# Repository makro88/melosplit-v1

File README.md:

# MeloSplit-v1

My first attempt at designing a custom keyboard, started as a challenge and as a potential new hobby.

Once I'm sure-ish this will actually work, I'm planning to build it as full wireless keyboard (thanks to [nice!nano](https://docs.nicekeyboards.com/#/nice!nano/))

Although it was supposed to be a simple ergo-split, it acquired a couple more functionalities along the way:
- wireless
- optional trrs
- hotswap MX switches
- RGB underglow
- RGB backlights
- rotary encoder
- reversible PCB

I lost count of how many times I've re-done the wiring in pcbnew, tried to keep it as tidy as possible!

### Kicad screenshots:

### Future plans:
- Make it work
- Cleaning up and adding some silks and text
- Case design

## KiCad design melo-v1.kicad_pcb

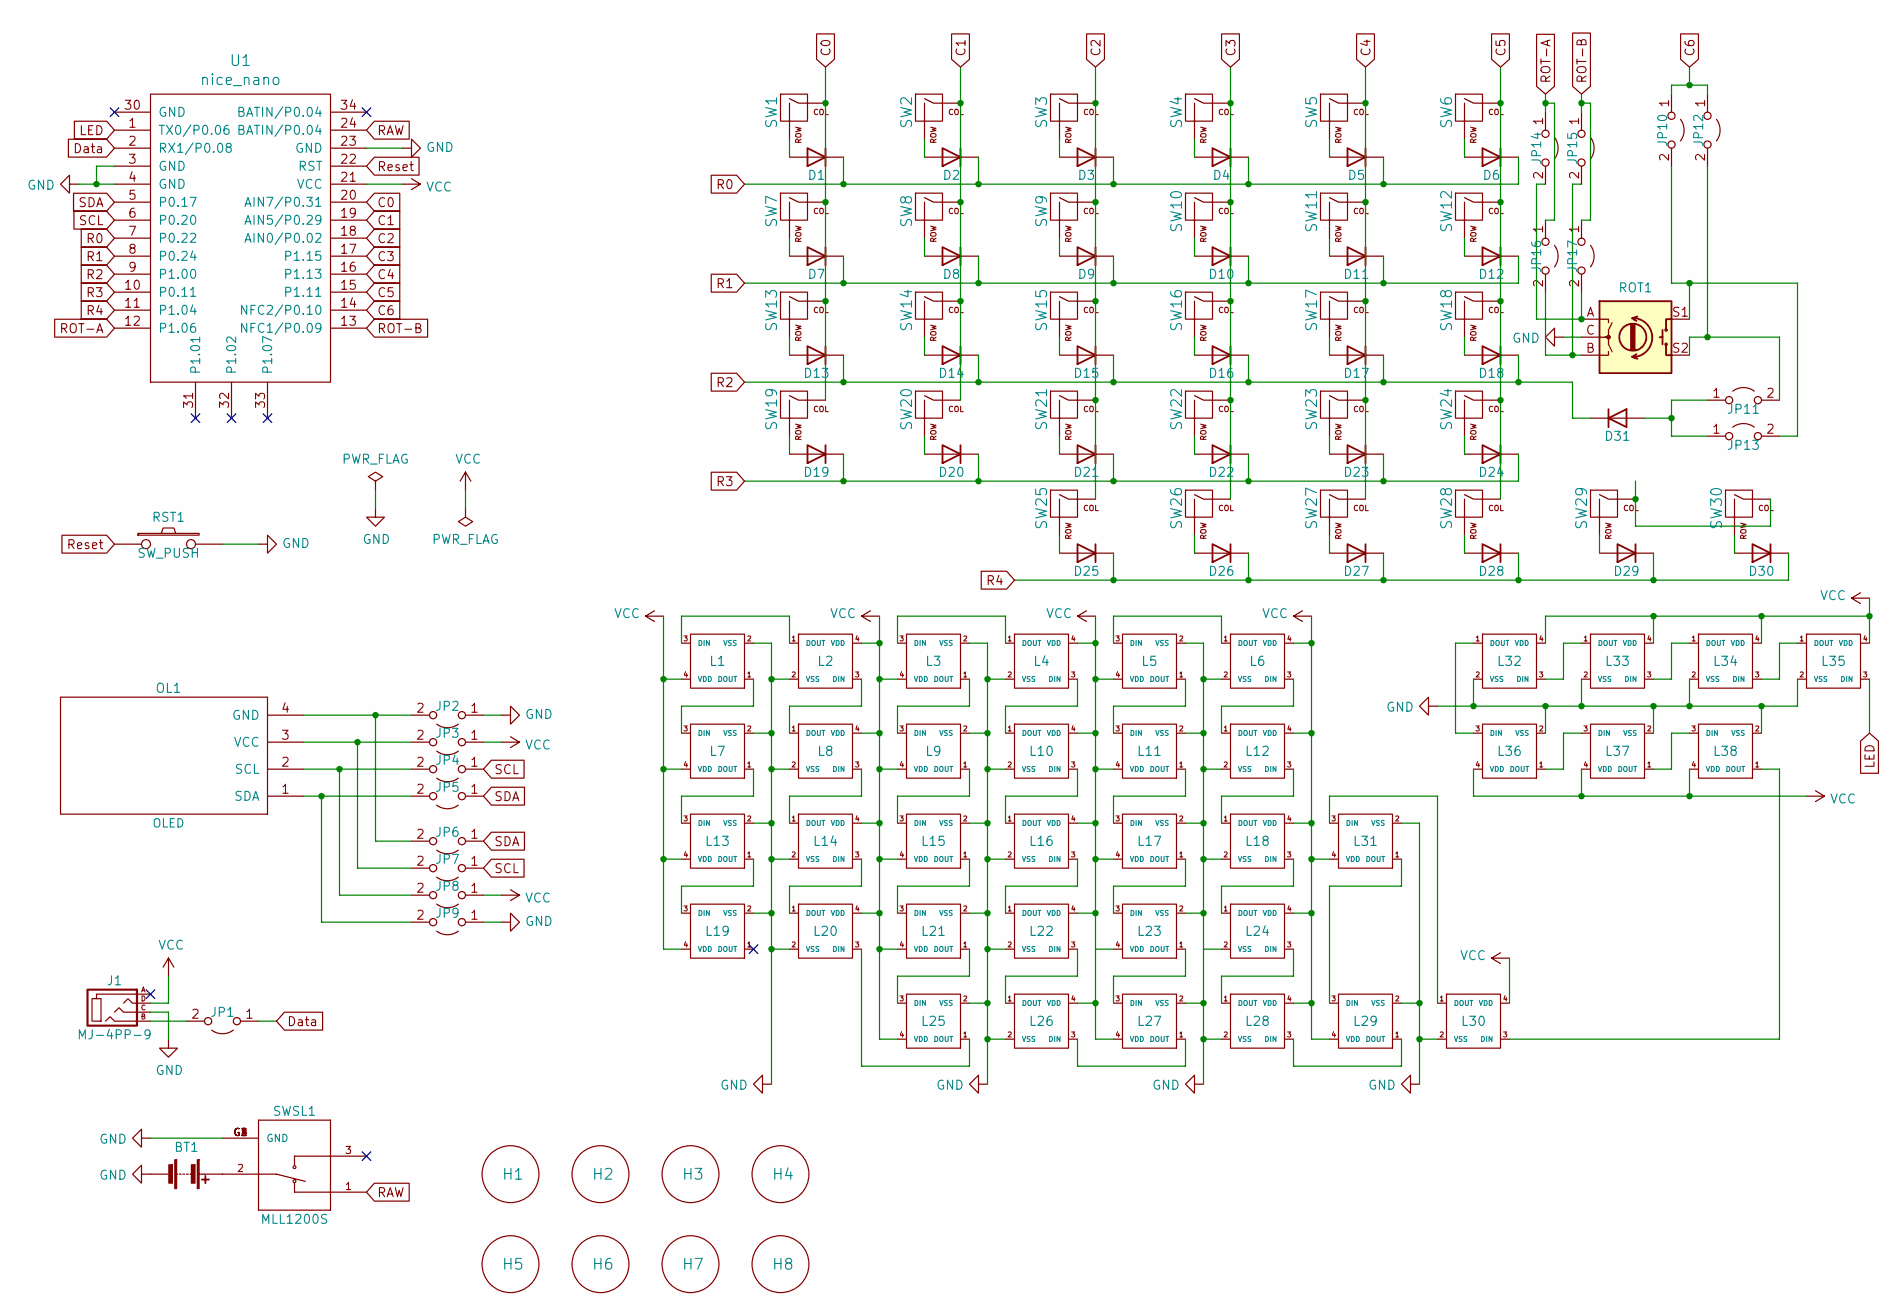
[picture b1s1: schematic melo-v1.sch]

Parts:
BT1: Battery; DF3A-3P-2DS_reversible
D1, D2, D3, D4, D5, D6, D7, D8, D9, D10, D11, D12, D13, D14, D15, D16, D17, D18, D19, D20, D21, D22, D23, D24, D25, D26, D27, D28, D29, D30, D31: D; D3_TH_SMD
H1, H2, H3, H4, H5, H6, H7, H8: Hole; HOLE
J1: MJ-4PP-9
JP1, JP2, JP3, JP4, JP5, JP6, JP7, JP8, JP9, JP10, JP11, JP12, JP13, JP14, JP15, JP16, JP17: Jumper_2_Open; Jumper
L1, L2, L3, L4, L5, L6, L7, L8, L9, L10, L11, L12, L13, L14, L15, L16, L17, L18, L19, L20, L21, L22, L23, L24, L25, L26, L27, L28, L29, L30, L31: SK6812MINI; YS-SK6812MINI-E_2sides
L32, L33, L34, L35, L36, L37, L38: SK6812MINI; SK6812MINI_underglow_rev
OL1: OLED
ROT1: Rotary_Encoder_Switch; RotaryEncoder_EC11
RST1: SW_PUSH; ResetSW
SW1, SW2, SW3, SW4, SW5, SW6, SW7, SW8, SW9, SW10, SW11, SW12, SW13, SW14, SW15, SW16, SW17, SW18, SW19, SW20, SW21, SW22, SW23, SW24, SW25, SW26, SW27, SW28, SW30: MX-NoLED; CherryMX_MidHeight_Hotswap
SW29: MX-NoLED; CherryMX_MidHeight_Hotswap_2U
SWSL1: MLL1200S; SW_MLL1200S
U1: nice_nano

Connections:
C0: SW1.1 (COL), SW7.1 (COL), SW13.1 (COL), SW19.1 (COL), U1.20 (AIN7/P0.31)
C1: SW2.1 (COL), SW8.1 (COL), SW14.1 (COL), SW20.1 (COL), U1.19 (AIN5/P0.29)
C2: SW3.1 (COL), SW9.1 (COL), SW15.1 (COL), SW21.1 (COL), SW25.1 (COL), U1.18 (AIN0/P0.02)
C3: SW4.1 (COL), SW10.1 (COL), SW16.1 (COL), SW22.1 (COL), SW26.1 (COL), U1.17 (P1.15)
C4: SW5.1 (COL), SW11.1 (COL), SW17.1 (COL), SW23.1 (COL), SW27.1 (COL), U1.16 (P1.13)
C5: SW6.1 (COL), SW12.1 (COL), SW18.1 (COL), SW24.1 (COL), SW28.1 (COL), U1.15 (P1.11)
C6: JP10.1 (A), JP12.1 (A), U1.14 (NFC2/P0.10)
Data: JP1.1 (A), U1.2 (RX1/P0.08)
LED: L35.3 (DIN), U1.1 (TX0/P0.06)
unnamed: BT1.1 (+), SWSL1.2
unnamed: D1.2 (A), SW1.2 (ROW)
unnamed: D2.2 (A), SW2.2 (ROW)
unnamed: D3.2 (A), SW3.2 (ROW)
unnamed: D4.2 (A), SW4.2 (ROW)
unnamed: D5.2 (A), SW5.2 (ROW)
unnamed: D6.2 (A), SW6.2 (ROW)
unnamed: D7.2 (A), SW7.2 (ROW)
unnamed: D8.2 (A), SW8.2 (ROW)
unnamed: D9.2 (A), SW9.2 (ROW)
unnamed: D10.2 (A), SW10.2 (ROW)
unnamed: D11.2 (A), SW11.2 (ROW)
unnamed: D12.2 (A), SW12.2 (ROW)
unnamed: D13.2 (A), SW13.2 (ROW)
unnamed: D14.2 (A), SW14.2 (ROW)
unnamed: D15.2 (A), SW15.2 (ROW)
unnamed: D16.2 (A), SW16.2 (ROW)
unnamed: D17.2 (A), SW17.2 (ROW)
unnamed: D18.2 (A), SW18.2 (ROW)
unnamed: D19.2 (A), SW19.2 (ROW)
unnamed: D20.2 (A), SW20.2 (ROW)
unnamed: D21.2 (A), SW21.2 (ROW)
unnamed: D22.2 (A), SW22.2 (ROW)
unnamed: D23.2 (A), SW23.2 (ROW)
unnamed: D24.2 (A), SW24.2 (ROW)
unnamed: D25.2 (A), SW25.2 (ROW)
unnamed: D26.2 (A), SW26.2 (ROW)
unnamed: D27.2 (A), SW27.2 (ROW)
unnamed: D28.2 (A), SW28.2 (ROW)
unnamed: D29.2 (A), SW29.2 (ROW)
unnamed: D30.2 (A), SW30.2 (ROW)
unnamed: D31.2 (A), JP11.1 (A), JP13.1 (A)
unnamed: J1.B, JP1.2 (B)
unnamed: JP2.2 (B), JP6.2 (B), OL1.4 (GND)
unnamed: JP3.2 (B), JP7.2 (B), OL1.3 (VCC)
unnamed: JP4.2 (B), JP8.2 (B), OL1.2 (SCL)
unnamed: JP5.2 (B), JP9.2 (B), OL1.1 (SDA)
unnamed: JP10.2 (B), JP13.2 (B), ROT1.S1
unnamed: JP11.2 (B), JP12.2 (B), ROT1.S2
unnamed: JP14.2 (B), JP17.2 (B), ROT1.A
unnamed: JP15.2 (B), JP16.2 (B), ROT1.B
unnamed: L1.1 (DOUT), L7.3 (DIN)
unnamed: L1.3 (DIN), L2.1 (DOUT)
unnamed: L2.3 (DIN), L8.1 (DOUT)
unnamed: L3.1 (DOUT), L9.3 (DIN)
unnamed: L3.3 (DIN), L4.1 (DOUT)
unnamed: L5.3 (DIN), L6.1 (DOUT)
unnamed: L4.3 (DIN), L10.1 (DOUT)
unnamed: L10.3 (DIN), L16.1 (DOUT)
unnamed: L11.1 (DOUT), L17.3 (DIN)
unnamed: L5.1 (DOUT), L11.3 (DIN)
unnamed: L6.3 (DIN), L12.1 (DOUT)
unnamed: L12.3 (DIN), L18.1 (DOUT)
unnamed: L13.1 (DOUT), L19.3 (DIN)
unnamed: L7.1 (DOUT), L13.3 (DIN)
unnamed: L8.3 (DIN), L14.1 (DOUT)
unnamed: L14.3 (DIN), L20.1 (DOUT)
unnamed: L15.1 (DOUT), L21.3 (DIN)
unnamed: L9.1 (DOUT), L15.3 (DIN)
unnamed: L16.3 (DIN), L22.1 (DOUT)
unnamed: L17.1 (DOUT), L23.3 (DIN)
unnamed: L18.3 (DIN), L24.1 (DOUT)
unnamed: L20.3 (DIN), L25.1 (DOUT)
unnamed: L21.1 (DOUT), L25.3 (DIN)
unnamed: L22.3 (DIN), L26.1 (DOUT)
unnamed: L23.1 (DOUT), L27.3 (DIN)
unnamed: L24.3 (DIN), L28.1 (DOUT)
unnamed: L26.3 (DIN), L27.1 (DOUT)
unnamed: L28.3 (DIN), L29.1 (DOUT)
unnamed: L29.3 (DIN), L31.1 (DOUT)
unnamed: L30.1 (DOUT), L31.3 (DIN)
unnamed: L30.3 (DIN), L38.1 (DOUT)
unnamed: L32.1 (DOUT), L36.3 (DIN)
unnamed: L32.3 (DIN), L33.1 (DOUT)
unnamed: L33.3 (DIN), L34.1 (DOUT)
unnamed: L34.3 (DIN), L35.1 (DOUT)
unnamed: L36.1 (DOUT), L37.3 (DIN)
unnamed: L37.1 (DOUT), L38.3 (DIN)
unnamed: SW29.1 (COL), SW30.1 (COL)
R0: D1.1 (K), D2.1 (K), D3.1 (K), D4.1 (K), D5.1 (K), D6.1 (K), U1.7 (P0.22)
R1: D7.1 (K), D8.1 (K), D9.1 (K), D10.1 (K), D11.1 (K), D12.1 (K), U1.8 (P0.24)
R2: D13.1 (K), D14.1 (K), D15.1 (K), D16.1 (K), D17.1 (K), D18.1 (K), D31.1 (K), U1.9 (P1.00)
R3: D19.1 (K), D20.1 (K), D21.1 (K), D22.1 (K), D23.1 (K), D24.1 (K), U1.10 (P0.11)
R4: D25.1 (K), D26.1 (K), D27.1 (K), D28.1 (K), D29.1 (K), D30.1 (K), U1.11 (P1.04)
RAW: SWSL1.1, U1.24 (BATIN/P0.04)
ROT-A: JP14.1 (A), JP16.1 (A), U1.12 (P1.06)
ROT-B: JP15.1 (A), JP17.1 (A), U1.13 (NFC1/P0.09)
Reset: RST1.1, U1.22 (RST)
SCL: JP4.1 (A), JP7.1 (A), U1.6 (P0.20)
SDA: JP5.1 (A), JP6.1 (A), U1.5 (P0.17)

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
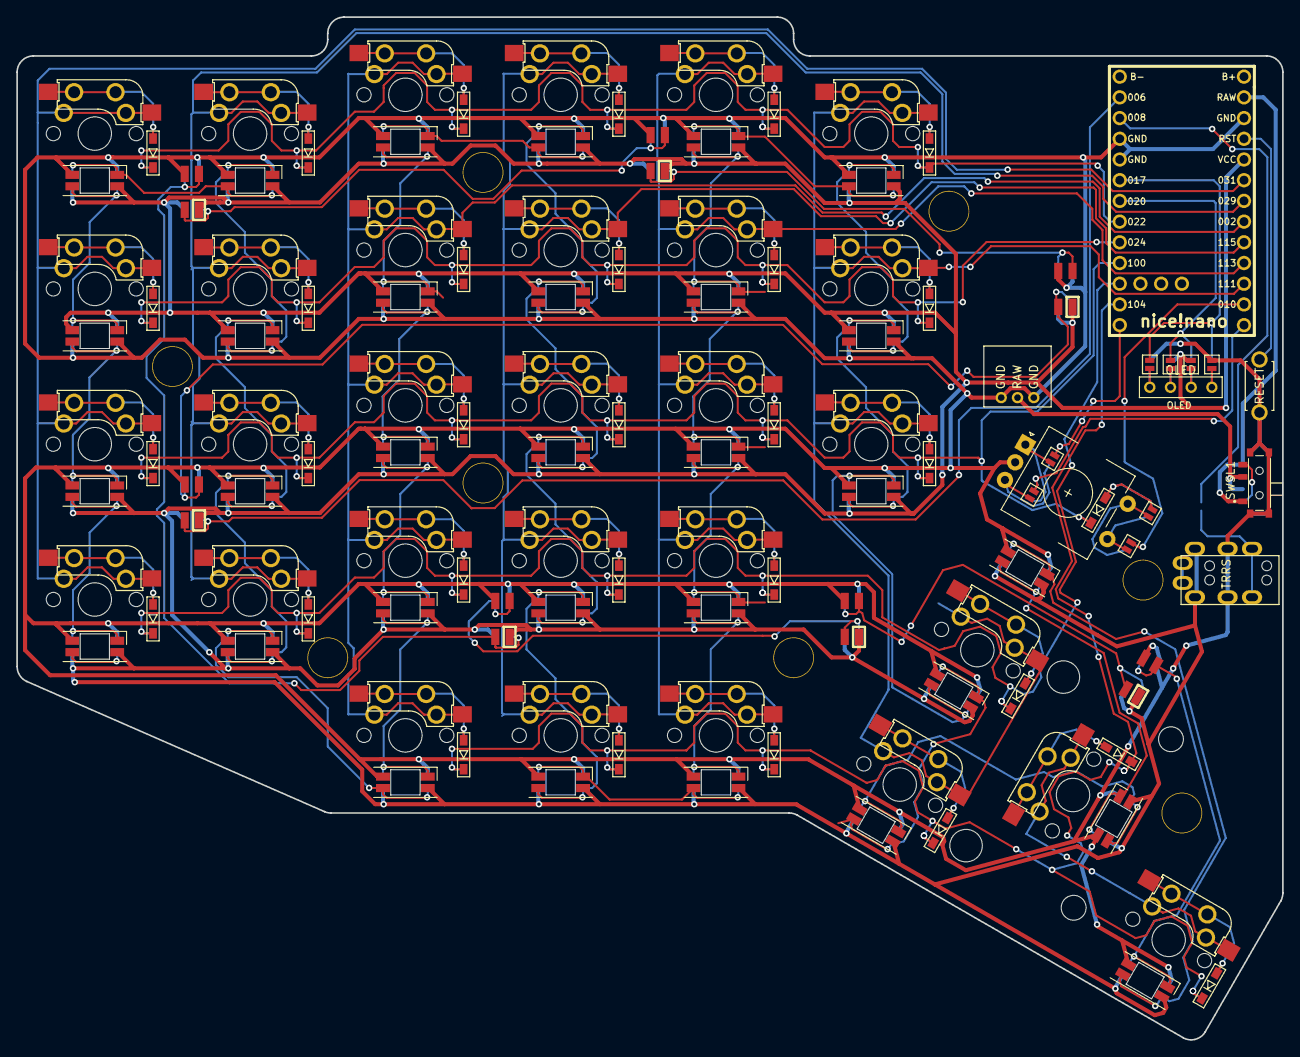
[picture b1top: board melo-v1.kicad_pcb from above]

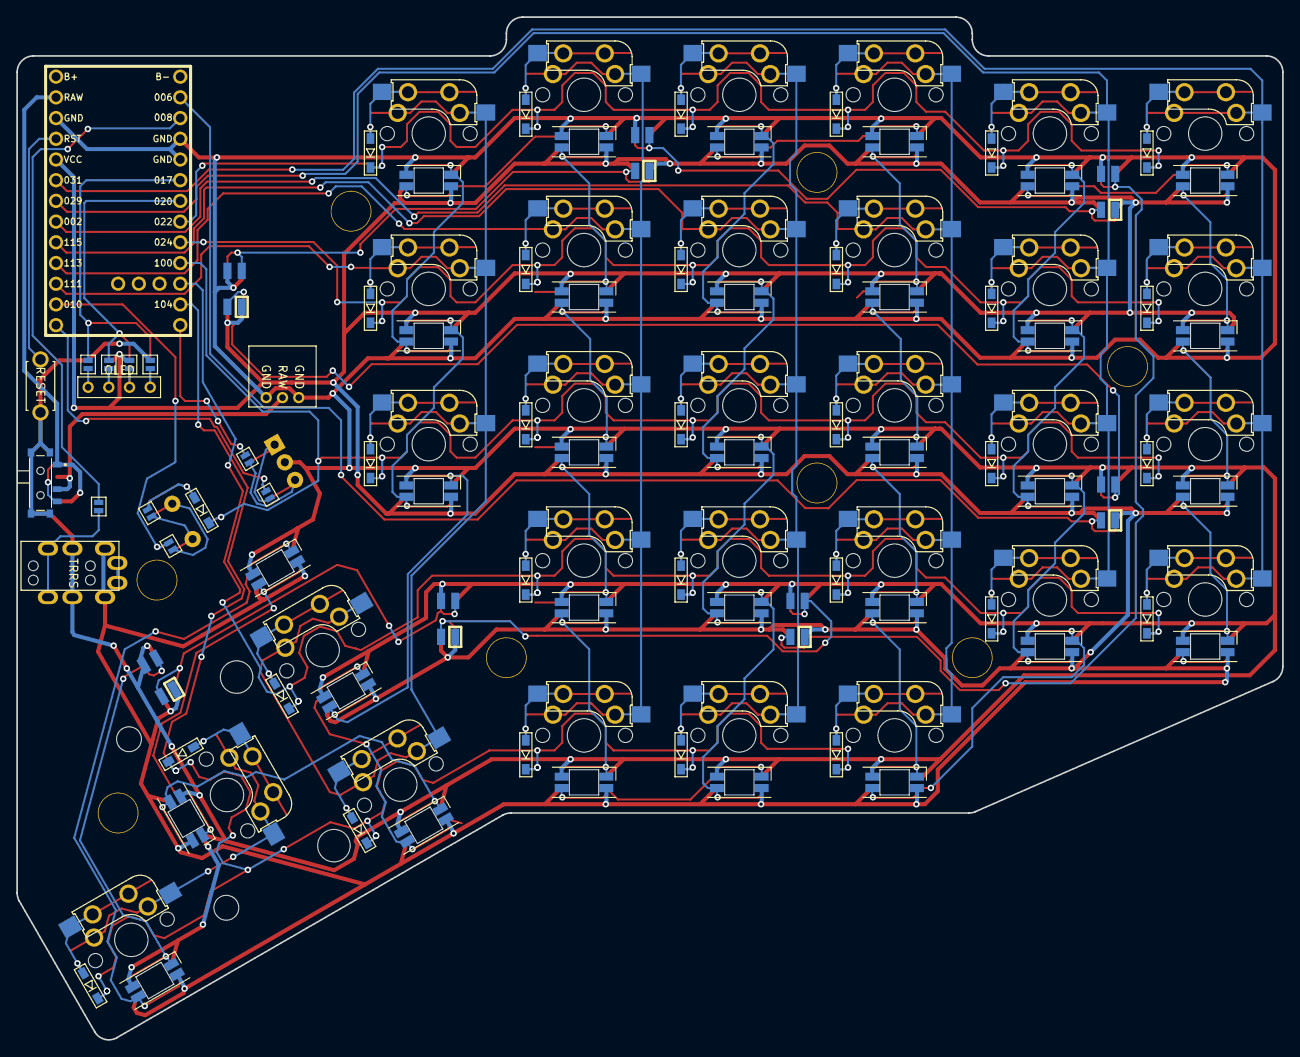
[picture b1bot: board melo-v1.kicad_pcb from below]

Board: 2 copper layers, 155.3 x 125.5 mm, 131 parts (10 on the bottom side), 101 nets.
